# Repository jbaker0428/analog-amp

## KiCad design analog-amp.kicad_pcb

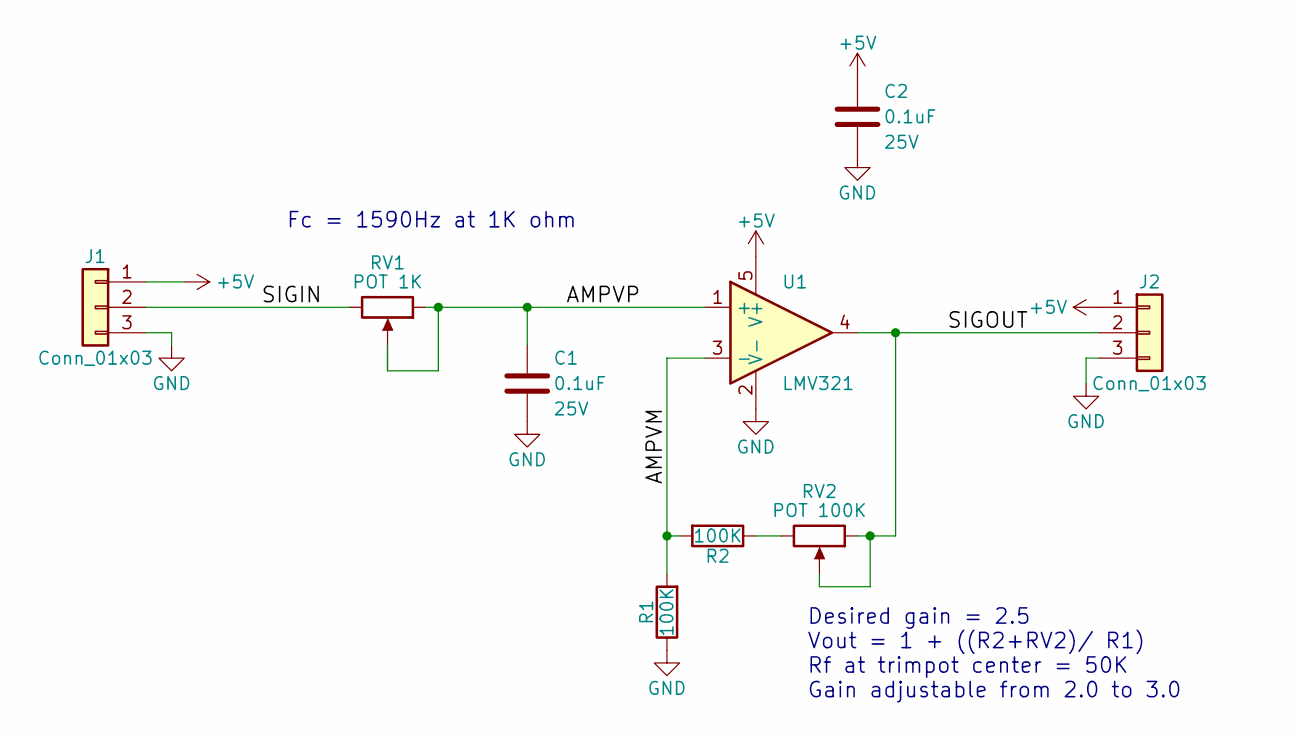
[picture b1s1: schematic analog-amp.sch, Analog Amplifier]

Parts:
C1, C2: 0.1uF; C_0402; Voltage 25V; PartNumber GRM155R61E104KA87D
J1, J2: Conn_01x03; Pin_Header_Straight_1x03_Pitch2.54mm; PartNumber 61300311121
R1, R2: 100K; R_0402; PartNumber RMCF0402FT100K
RV1: POT 1K; Potentiometer_Trimmer_Copal_CT-6EP; PartNumber CT6EP102
RV2: POT 100K; Potentiometer_Trimmer_Copal_CT-6EP; PartNumber CT6EP104
U1: LMV321; SOT-23-5; PartNumber LMV321LILT

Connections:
+5V: C2.1, J1.1, J2.1, U1.5 (V+)
/AMPVM: R1.2, R2.2, U1.3 (-)
/AMPVP: C1.1, RV1.1, RV1.2, U1.1 (+)
/SIGIN: J1.2, RV1.3
/SIGOUT: J2.2, RV2.1, RV2.2, U1.4
GND: C1.2, C2.2, J1.3, J2.3, R1.1, U1.2 (V-)
unnamed: R2.1, RV2.3

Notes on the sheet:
Desired gain = 2.5 Vout = 1 + ((R2+RV2)/ R1) Rf at trimpot center = 50K Gain adjustable from 2.0 to 3.0
Fc = 1590Hz at 1K ohm

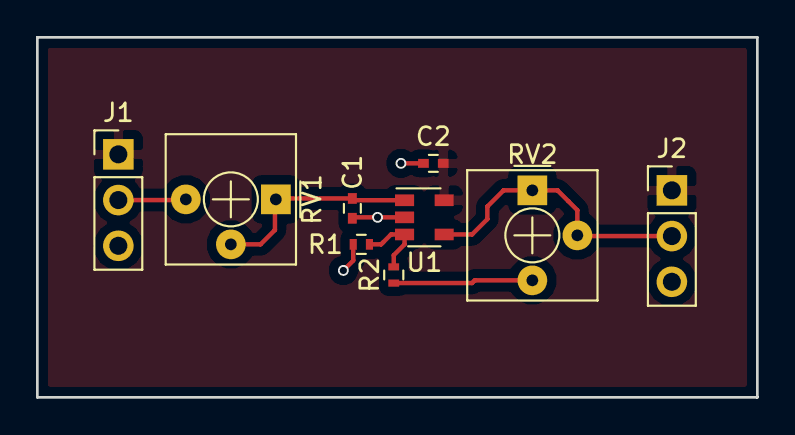
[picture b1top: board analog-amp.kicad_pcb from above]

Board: 2 copper layers, 40.0 x 20.0 mm, 9 parts (0 on the bottom side), 7 nets.

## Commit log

2017-10-31 Initial commit.
2017-10-31 Adding schematic PDF.
2017-10-31 Adding BOM.
